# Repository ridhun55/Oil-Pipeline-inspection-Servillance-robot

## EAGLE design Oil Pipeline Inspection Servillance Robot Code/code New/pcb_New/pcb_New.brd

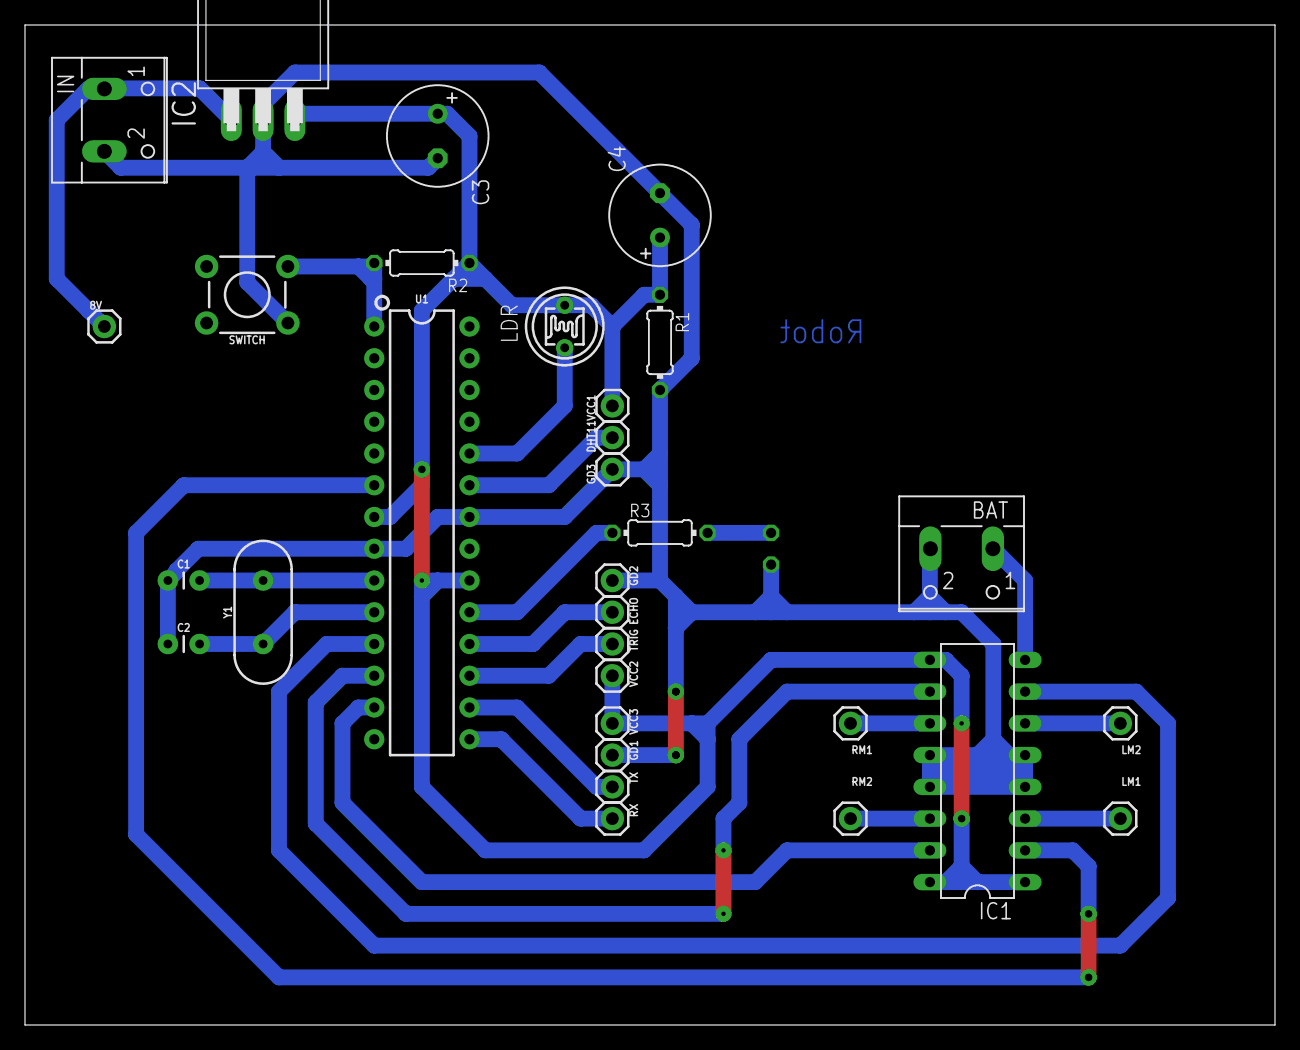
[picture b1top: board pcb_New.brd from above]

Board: 2 copper layers, 100.0 x 80.0 mm, 32 parts (1 on the bottom side), 23 nets.

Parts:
8V: 8v; 1X01
BAT: W237-102
C1, C2: 22pF; CAP-PTH-2.54
C3: 1000uf; E3,5-8
C4: E3,5-8
DHT11: DHT11; 1X01
ECHO: 1X01
GD1, GD2, GD3: 1X01
IC1: L293D; DIL16
IC2: 7805T; TO220H
IN: W237-102
LDR: A1050_09; T0-46-A10XX
LED1: LED_LD260
LM1, LM2: 1X01
R1: 10k; 0204/7
R2: 10K; 0204/7
R3: 330; 0204/7
RM1, RM2: 1X01
RX: 1X01
SWITCH: Reset; TACTILE_SWITCH_PTH_6.0MM
TRIG: 1X01
TX: 1X01
U1: 328P; DIP28
VCC1, VCC2, VCC3: 1X01
Y1: 16MHz; HC49US

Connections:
GND: BAT.2, C1.1, C2.1, C3.-, C4.-, GD1.1, GD2.1, GD3.1, IC1.4, IC1.5, IC1.12, IC1.13, IC2.2, IN.2, LED1.K, R1.2, SWITCH.1, U1.8, U1.22
unnamed: C1.2, U1.9, Y1.2
unnamed: C2.2, U1.10, Y1.1
unnamed: RX.1, U1.15
unnamed: R2.2, SWITCH.3, U1.1
unnamed: TX.1, U1.16
unnamed: ECHO.1, U1.18
unnamed: TRIG.1, U1.17
unnamed: LDR.2, U1.24
unnamed: DHT11.1, U1.23
unnamed: LED1.A, R3.2
unnamed: R3.1, U1.19
unnamed: IC1.2, U1.6
unnamed: BAT.1, IC1.8
unnamed: IC1.6, LM2.1
unnamed: 8V.1, IC2.1, IN.1
unnamed: IC1.3, LM1.1
unnamed: IC1.14, RM2.1
unnamed: IC1.7, U1.11
unnamed: IC1.11, RM1.1
unnamed: IC1.10, U1.12
unnamed: IC1.15, U1.13
VCC: C3.+, C4.+, IC1.1, IC1.9, IC1.16, IC2.3, LDR.1, R1.1, R2.1, U1.7, U1.20, VCC1.1, VCC2.1, VCC3.1

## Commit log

2021-06-30 Add flowchart

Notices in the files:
parts and their libraries:
SparkFun-Capacitors: Licensing: Creative Commons ShareAlike 4.0 International - https://creativecommons.org/licenses/by-sa/4.0
